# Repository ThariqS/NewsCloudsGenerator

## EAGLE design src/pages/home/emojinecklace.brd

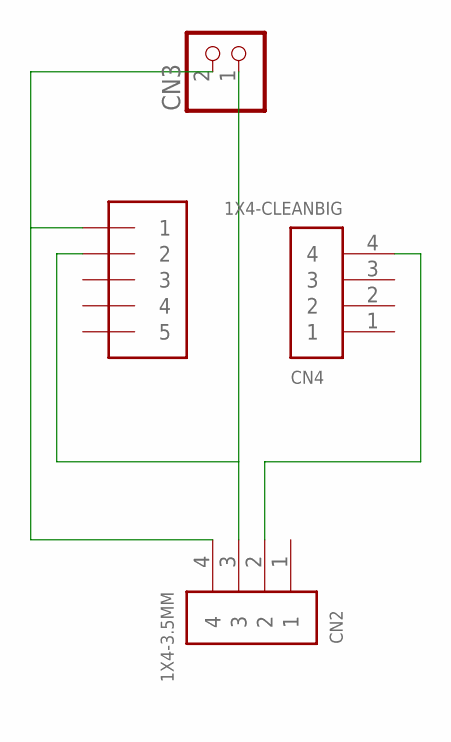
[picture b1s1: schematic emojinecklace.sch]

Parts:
CN2: 1X4-3.5MM; 1X04-3.5MM
CN3: JST_2PIN-THM; JST-PH-2-THM
CN4: 1X4-CLEANBIG; 1X04-CLEANBIG
J1: 1X5; 1X05-3.5MM

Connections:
B0: CN2.2, CN4.4
unnamed: CN2.4, CN3.2 (1), J1.1
unnamed: CN2.3, CN3.1 (2), J1.2

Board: 2 copper layers, 4 parts (0 on the bottom side), 3 nets, no tracks yet.

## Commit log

2016-02-11 adding stuff
2016-03-01 making graph data work
2016-03-01 adding related terms API
2016-03-02 got the graph working pretty nicely, I used a loop implementation but might clean it up a bit with a map function
2016-03-03 trying to add related terms
2016-03-03 got the related terms working nicely, might still need some formatting though
2016-03-03 Adding multiple sources
2016-03-09 Hard coded in a chart of trump vs rubio vs cruz. It could still use some styling and I'm having an issue with the labels on the axis, but I think its a pretty good example. I'll add a pic
2016-03-21 still having some bugs, one of the lines isn't showing up even though the data points are???
2016-03-31 graph is MOTHERFUCKING working. Need to make more line colors, style better, and do the date range , but the base is solid finally
2016-03-31 just added a function that loops over the three line colors, so you can have as many lines as you want. We should def come up with some new colors though
2016-04-07 adding result tabs
2016-04-07 adding a loader
2016-04-08 just made it better yay go team
2016-04-08 iscolated moment objects for date queries, but not exactly sure what to do with them yet
2016-04-08 this stuff is all good
2016-04-08 fixing package json
2016-04-08 fixing node engine version
2016-04-08 removing procfile
2016-04-08 renaming
2016-04-08 adding node version
2016-04-08 forgot comma
2016-04-10 readding procfile
2016-04-10 package.json
2016-04-10 disable node_modules cache
2016-04-10 webpack progress
2016-04-10 fixing radium
2016-04-10 typo
2016-04-10 making things better
2016-04-10 Making a results page
2016-04-10 https url
2016-04-10 herokuapp.com
2016-04-11 percentages work better
2016-04-11 changed the line colors up
2016-04-14 got a nice date range box going - the formatting for hovering over it is kinda weird I'm workign on that now
2016-04-21 finished the styling, let me know what you think
